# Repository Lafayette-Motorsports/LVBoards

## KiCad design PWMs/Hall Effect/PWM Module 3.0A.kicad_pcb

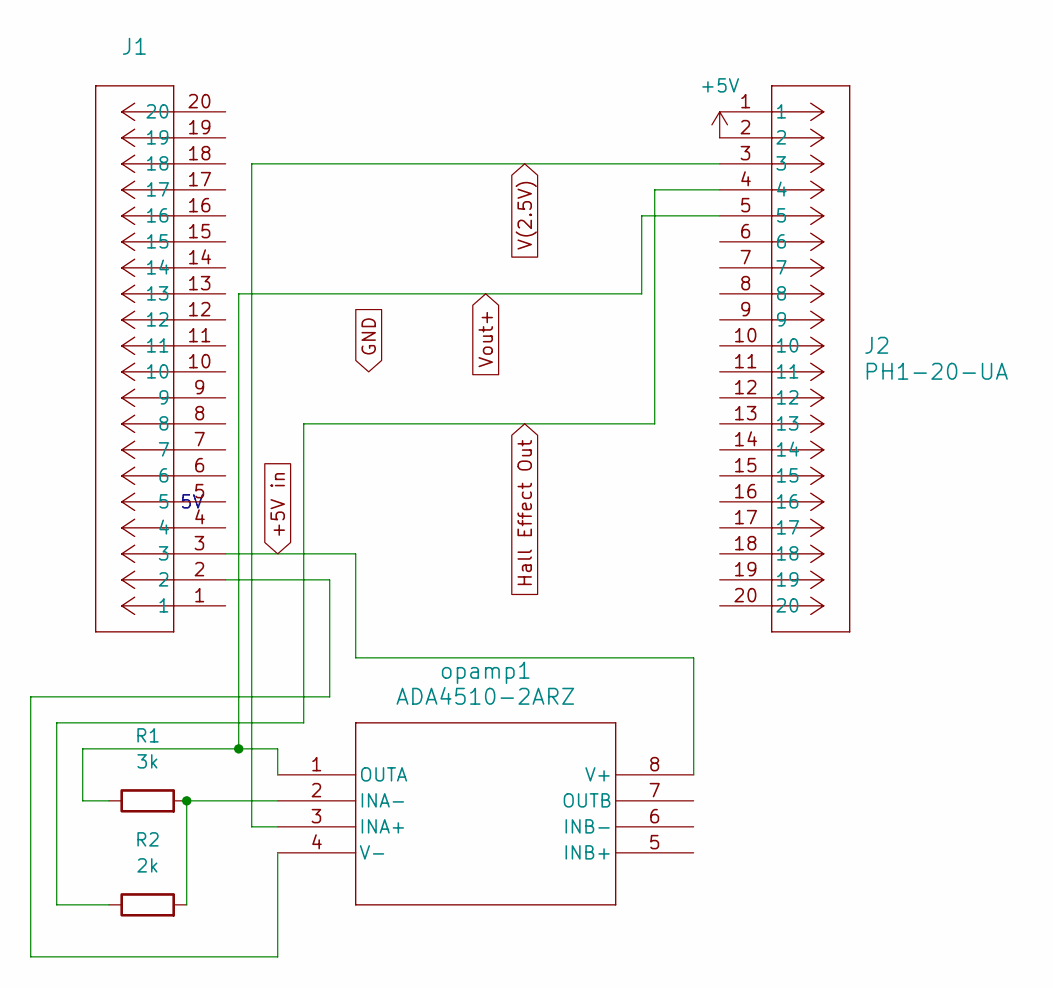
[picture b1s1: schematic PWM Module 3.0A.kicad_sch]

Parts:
J1, J2: PH1-20-UA; PinHeader_1x20_P2.54mm_Vertical
R1: 3k; R_Axial_DIN0207_L6.3mm_D2.5mm_P10.16mm_Horizontal
R2: 2k; R_Axial_DIN0207_L6.3mm_D2.5mm_P10.16mm_Horizontal
opamp1: ADA4510-2ARZ; R-8_ADI

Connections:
+5V: J2.2
+5V in: J1.3, opamp1.8 (V+)
Hall Effect Out: J2.4, R2.1
unnamed: R1.2, R2.2, opamp1.2 (INA-)
unnamed: J1.2, opamp1.4 (V-)
V(2.5V): J2.3, opamp1.3 (INA+)
Vout+: J2.5, R1.1, opamp1.1 (OUTA)

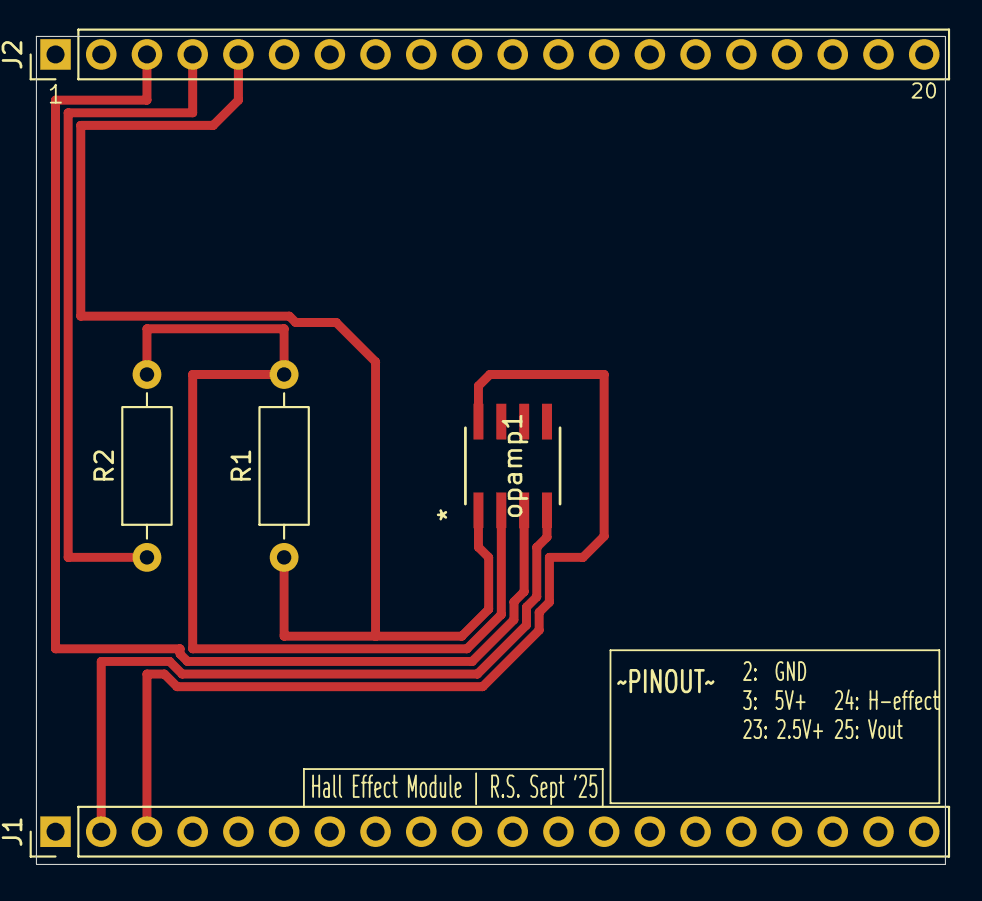
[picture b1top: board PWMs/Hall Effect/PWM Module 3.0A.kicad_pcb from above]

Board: 2 copper layers, 50.5 x 46.0 mm, 5 parts (0 on the bottom side), 6 nets.

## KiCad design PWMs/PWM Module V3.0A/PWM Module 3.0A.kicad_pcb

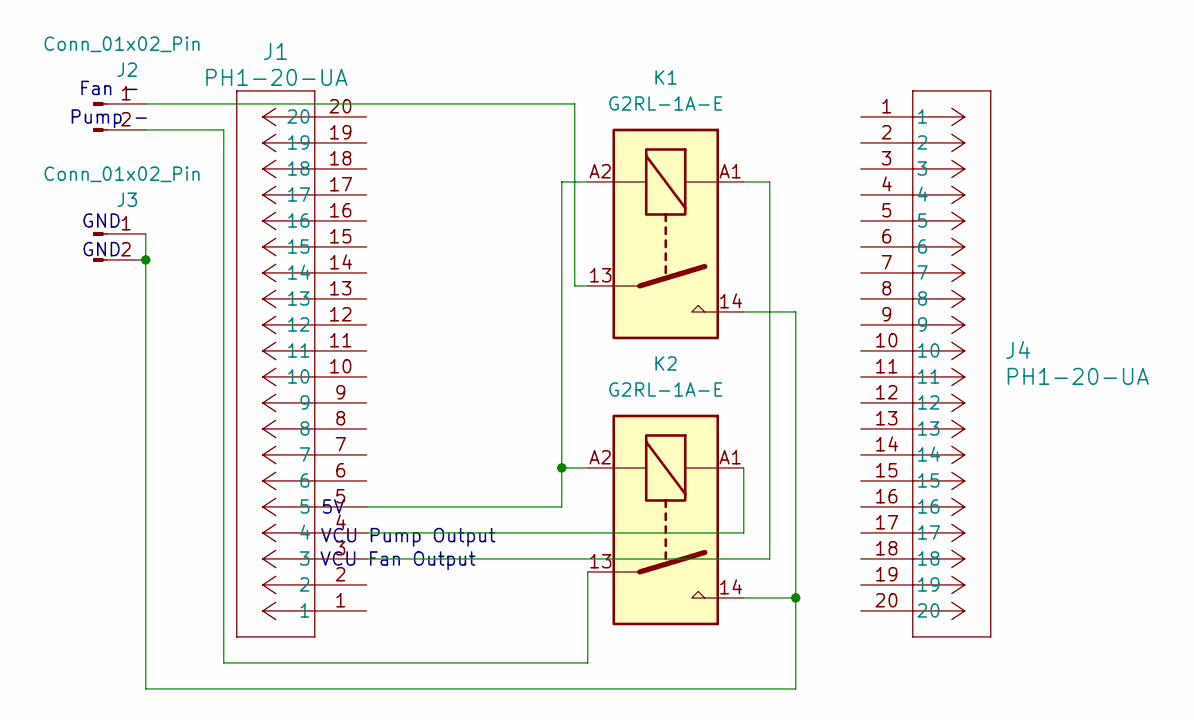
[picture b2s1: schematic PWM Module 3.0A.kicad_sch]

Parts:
J1, J4: PH1-20-UA; PinHeader_1x20_P2.54mm_Vertical
J2, J3: Conn_01x02_Pin; TerminalBlock_Phoenix_PT-1,5-2-5.0-H_1x02_P5.00mm_Horizontal
K1, K2: G2RL-1A-E; Relay_SPST_Omron_G2RL-1A-E

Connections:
unnamed: J1.3, K1.A1
unnamed: J1.4, K2.A1
unnamed: J1.5, K1.A2, K2.A2
unnamed: J2.1, K1.13
unnamed: J2.2, K2.13
unnamed: J3.1, J3.2, K1.14, K2.14

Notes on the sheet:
GND
Pump -
VCU Fan Output
Fan -
VCU Pump Output

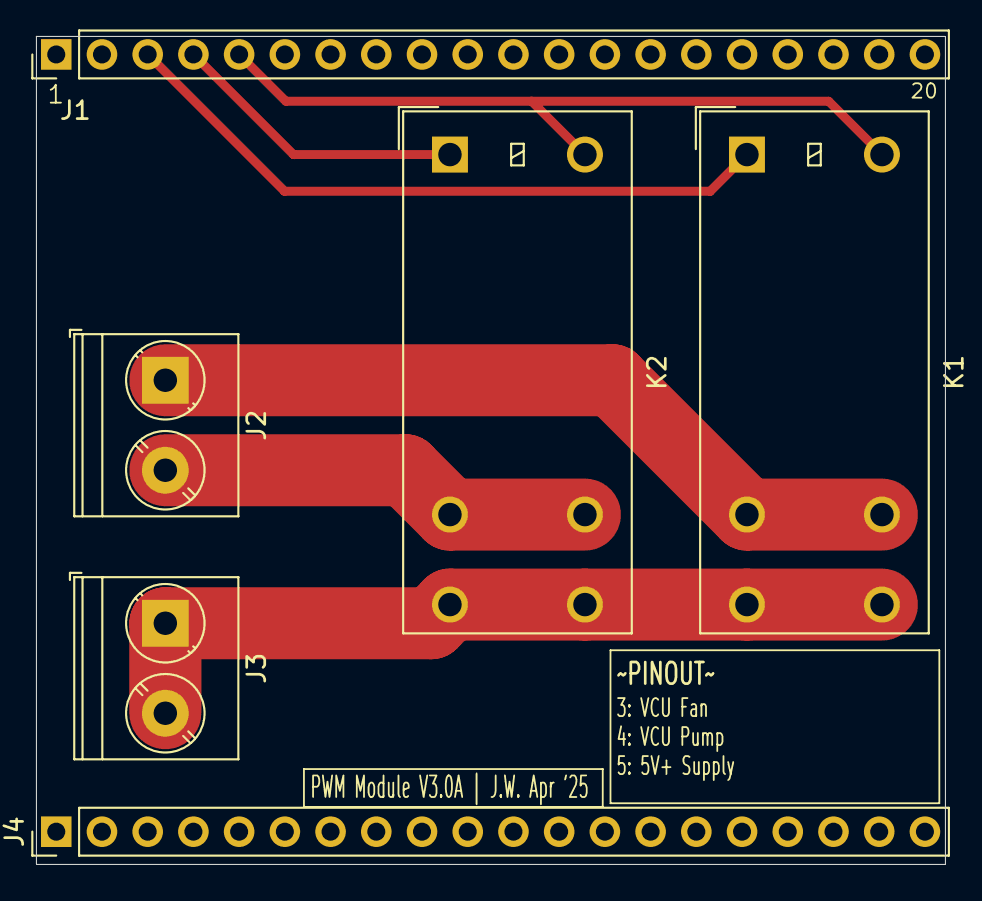
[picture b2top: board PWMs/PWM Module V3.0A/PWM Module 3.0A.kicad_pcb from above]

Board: 2 copper layers, 50.5 x 46.0 mm, 6 parts (0 on the bottom side), 6 nets.

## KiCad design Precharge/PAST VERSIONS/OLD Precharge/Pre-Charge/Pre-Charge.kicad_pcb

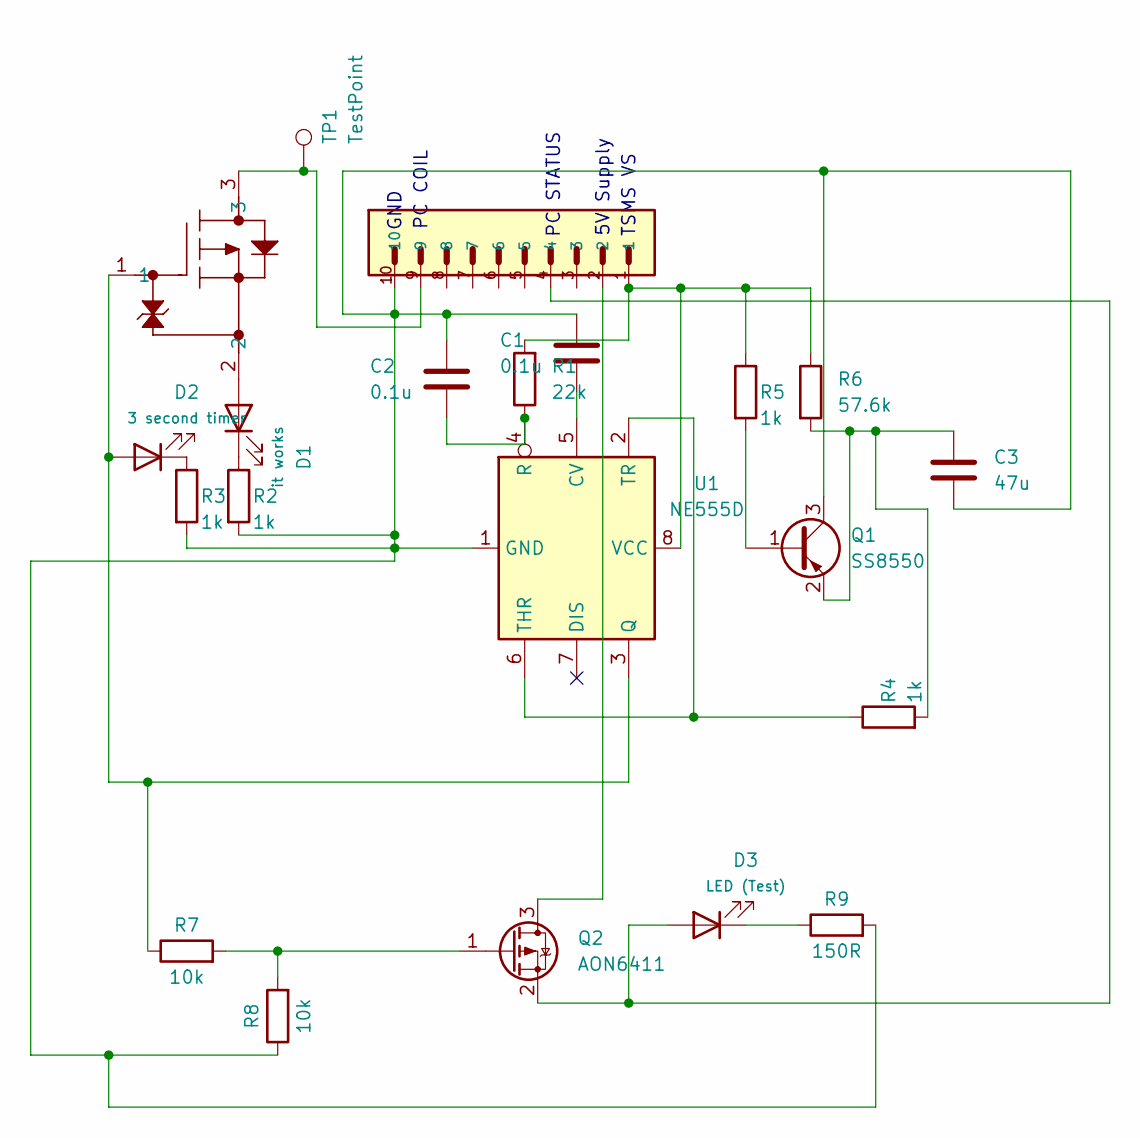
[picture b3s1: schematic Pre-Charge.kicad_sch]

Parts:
C1, C2: 0.1u; CAP_CL31_SAM
C3: 47u; CAP_CL32_SAM
D1: it works; LED_AP3216SYD_KNB
D2: 3 second timer; LED_AP3216SYD_KNB
D3: LED (Test); LED_AP3216SYD_KNB
J1: PH1-10-UA; 1X10-2.54MM-THT
MOSFET1: SSM3J56MFV_L3F; VESM_TOS
Q1: SS8550; SOT-23_MCC
Q2: AON6411; VESM_TOS
R1: 22k; STA_RMCF0805_STP
R2, R3, R4, R5: 1k; STA_RMCF0603_STP
R6: 57.6k; RES_ERJ1GNF5762C
R7, R8: 10k; RESC0603X26N
R9: 150R; RC0805N_YAG
TP1: TestPoint; TestPoint_Loop_D2.60mm_Drill1.6mm_Beaded
U1: NE555D; SOIC127P599X175-8N

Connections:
unnamed 0: D1.2 (A), MOSFET1.2; also elsewhere on the board
unnamed: D1.1 (K), R2.1
unnamed 2: D2.2 (A), MOSFET1.1, R7.1, U1.3 (Q); also elsewhere on the board
unnamed: D2.1 (K), R3.1
unnamed: D3.2 (A), J1.4, Q2.2 (S)
unnamed: D3.1 (K), R9.1
unnamed 6: J1.9, MOSFET1.3, TP1.1; also elsewhere on the board
unnamed: Q1.1 (B), R5.2
unnamed: C1.1, C2.1, C3.2, J1.10, Q1.3 (C), R2.2, R3.2, R8.1, R9.2, U1.1 (GND)
unnamed: C3.1, Q1.2 (E), R4.2, R6.2
unnamed: J1.2, Q2.3 (D)
unnamed: Q2.1 (G), R7.2, R8.2
unnamed: C1.2, U1.5 (CV)
unnamed: C2.2, R1.1, U1.4 (R)
unnamed: R4.1, U1.2 (TR), U1.6 (THR)
unnamed: J1.1, R1.2, R5.1, R6.1, U1.8 (VCC)

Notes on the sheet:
GND
PC COIL
TSMS VS
PC STATUS
5V Supply

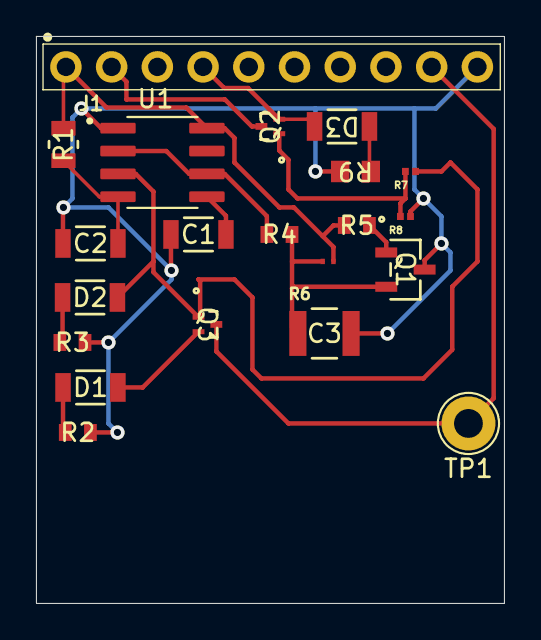
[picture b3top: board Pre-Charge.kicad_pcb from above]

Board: 2 copper layers, 26.0 x 31.5 mm, 21 parts (0 on the bottom side), 16 nets.

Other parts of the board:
Q3: SSM3J56MFV_L3F; VESM_TOS

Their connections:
unnamed 0: Q3.2; also elsewhere on the board
unnamed 2: Q3.1; also elsewhere on the board
unnamed 6: Q3.3; also elsewhere on the board

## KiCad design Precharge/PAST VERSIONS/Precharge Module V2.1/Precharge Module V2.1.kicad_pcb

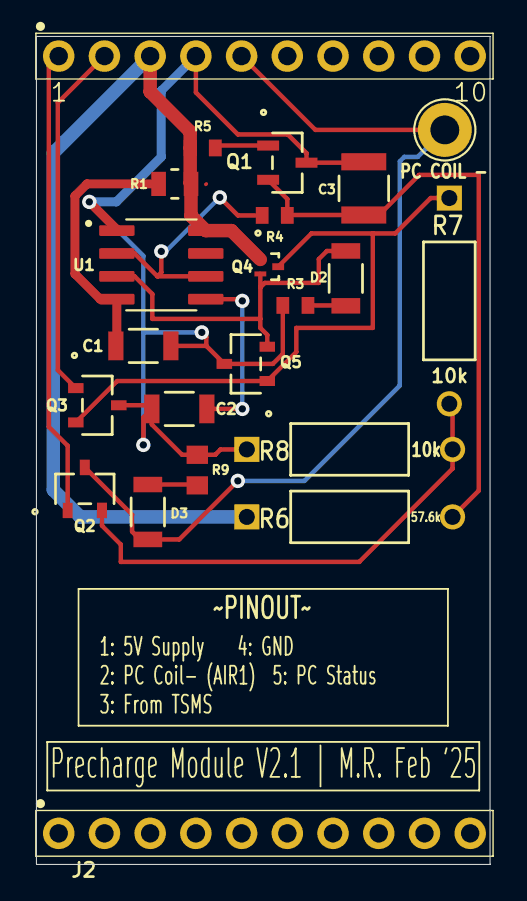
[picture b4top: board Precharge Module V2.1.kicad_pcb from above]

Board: 2 copper layers, 25.2 x 46.0 mm, 22 parts (0 on the bottom side), 15 nets.

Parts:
C1, C2: 0.1u; CAP_CL31_SAM
C3: 47u; CAP_CL32_SAM
D2: 3 second timer; LED_AP3216SYD_KNB
D3: LED (Test); LED_AP3216SYD_KNB
J1, J2: PH1-10-UA; 1X10-2.54MM-THT
PC COIL -: TestPoint; TestPoint_Loop_D2.60mm_Drill1.6mm_Beaded
Q1: SS8550; SOT-23_MCC
Q2, Q3, Q5: NMOS; SOT23_INF
Q4: PMOS; VESM_TOS
R1: 22k; STA_RMCF0805_STP
R3, R4, R5: 1k; STA_RMCF0603_STP
R6: 57.6k; STA_CF14_STP
R7, R8: 10k; STA_CF14_STP
R9: 150R; RC0805N_YAG
U1: NE555D; SOIC127P599X175-8N

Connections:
unnamed: D2.2 (A), Q4.2 (G), Q5.2 (G), U1.3 (Q)
unnamed: D2.1 (K), R3.1
unnamed: D3.2 (A), J1.5, PC COIL -.1, Q2.3 (S)
unnamed: D3.1 (K), R9.2
unnamed: Q1.1 (B), R5.2
unnamed: C1.2, C2.2, C3.2, J1.4, Q1.3 (C), Q3.3 (S), Q5.3 (S), R3.2, R8.1, R9.1, U1.1 (GND)
unnamed: C3.1, Q1.2 (E), R4.2, R6.2
unnamed: J1.1, Q2.1 (D)
unnamed: Q2.2 (G), R7.2, R8.2
unnamed: J1.2, Q3.1 (D)
unnamed: Q3.2 (G), Q4.3 (S), Q5.1 (D), R7.1
unnamed: J1.3, Q4.1 (D), R1.2, R5.1, R6.1, U1.8 (VCC)
unnamed: C2.1, U1.5 (CV)
unnamed: C1.1, R1.1, U1.4 (R)
unnamed: R4.1, U1.2 (TR), U1.6 (THR)

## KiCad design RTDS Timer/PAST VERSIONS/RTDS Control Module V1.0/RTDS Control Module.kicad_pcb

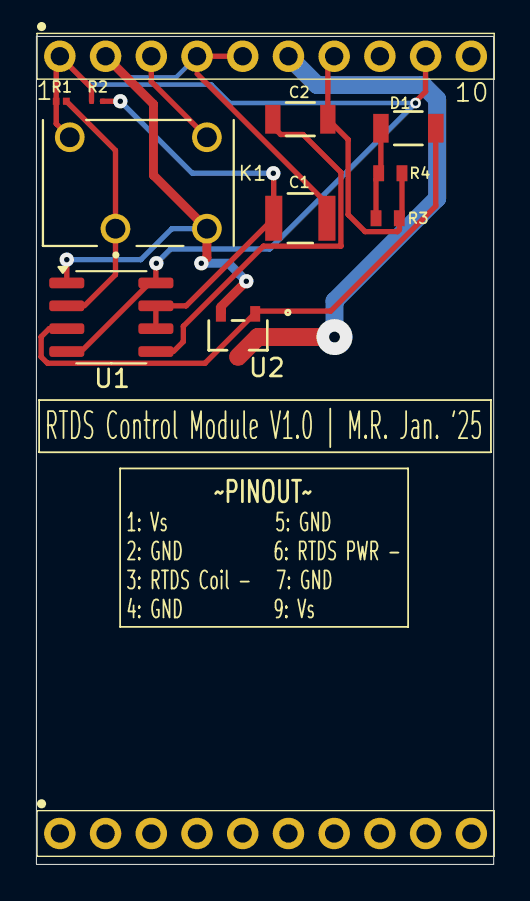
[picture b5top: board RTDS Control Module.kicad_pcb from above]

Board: 2 copper layers, 25.4 x 46.0 mm, 12 parts (0 on the bottom side), 9 nets.

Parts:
C1: 47u; CAP_CL32_SAM
C2: 0.1u; CAP_CL31_SAM
D1: LED (Test); LED_AP3216SYD_KNB
J1, J1#2: PH1-10-UA; 1X10-2.54MM-THT
K1: G6L-1P_DC5; RELAY_G6L-1P_DC5
R1: 10k; RESC0603X26N
R2: 57.6k; RES_ERJ1GNF5762C
R3, R4: 1k; STA_RMCF0603_STP-L
U1: NE555D; SOIC-8_3.9x4.9mm_P1.27mm
U2: IRLML2060TRPBF; SOT23_INF

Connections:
/GND: C1.2, C2.2, J1#2.2, J1#2.4, J1#2.5, J1#2.7, K1.4, R3.2, R4.2, U1.1 (GND), U2.2 (S)
/Vs: J1#2.1, J1#2.9, K1.8, R1.1, R2.1, U1.4 (R), U1.8 (VCC)
unnamed: D1.2 (A), U1.3 (Q), U2.1 (G)
unnamed: D1.1 (K), R3.1, R4.1
unnamed: J1#2.3, K1.5
unnamed: C2.1, U1.5 (CV)
unnamed: C1.1, R2.2, U1.6 (THR), U1.7 (DIS)
unnamed: K1.2, R1.2, U1.2 (TR)
unnamed: J1#2.6, U2.3 (D)
